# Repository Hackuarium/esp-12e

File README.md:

| GPIO  |            |           |         |                                           |            | Arduino |                  |
| ----- | ---------- | --------- | ------- | ----------------------------------------- | ---------- | ------- | ---------------- |
| 0     |            | SPI_CS2   |         | HIGH: normal, LOW: programming            | LOW / HIGH | D3      | button LOW / BLK |
| 1     |            | SPI_CS1   | U0_TXD  |                                           | TX         | D10     | TX               |
| 2     |            |           | U1_TXD  | on boot HIGH for programming              | HIGH       | D4      | One WIRE (HIGH)  |
| 3     |            |           | U0_RXD  |                                           | RX         | D9      | RX               |
| 4     |            |           |         |                                           | I2C        | D2/SDA  | SDA              |
| 5     |            |           |         |                                           | I2C        | D1/SCL  | SCL              |
| 6     | SDIO_CLK   | SPI_CLK   |         | used to connect flash 4MB                 | reserved   |
| 7     | SDIO_DATA0 | SPI_MISO  |         | used to connect flash 4MB                 | reserved   |
| 8     | SDIO_DATA1 | SPI_MOSI  | U1_RXD  | used to connect flash 4MB                 | reserved   |
| 9     | SDIO_DATA2 | SPI_HD    | HSPI_HD | used to connect flash 4MB                 | reserved   |
| 10    | SDIO_DATA3 | SPI_WP    | HSPI_WP | used to connect flash 4MB                 | reserved   |
| 11    | SDIO_CMD   | SPI_CS0   |         | used to connect flash 4MB                 | reserved   |
| 12    | MTDI       | HSPI_MISO |         |                                           | MISO       | D6      | PWM R            |
| 13    | MTCK       | HSPI_MOSI | U0_CTS  |                                           | MOSI       | D7      | PWM G            |
| 14    | MTMS       | HSPI_CLK  |         |                                           | CLK        | D5      | PWM B            |
| 15    | MTDO       | HSPI_CS   | U0_RTS  | on boot LOW for programming               | LOW / CS   | D8      | PWM W (LOW)      |
| 16    | XPD_DCDC   |           |         | sleep mode to EXT_RSTB (allow deep sleep) | RESET      | D0      | RST              |
| 17    | ADC        |           |         | voltage 0—1.0V                            | Battery    | A0      |
| RESET |            |           |         |                                           |            |         | Pull UP          |

15: WS2812, adressable led

Read information on: https://www.kloppenborg.net/images/blog/esp8266/esp8266-esp12e-specs.pdf

Available pins: http://www.rabbithacks.com/esp8266/esp12-e-directly-usable-gpio-pins/

PWM on all the pins !
HSPI (screen or other): 12 13 14 15
PWM: R12 G15 B13
ADC: TOUT
I2C: SCL14 SDA2

## Flashing board ?

You need to maintain `SW2` while pressing `SW1` (reset) in order to set the ESP-12E in programing mode.

- https://hackaday.com/2015/03/18/how-to-directly-program-an-inexpensive-esp8266-wifi-module/
- https://easyeda.com/olegos76/ESP8266_arduino_IDE-d4457f9439fd4de7a8970ff36a4957d6
- https://www.instructables.com/id/3-Simple-Ways-of-Programming-an-ESP8266-12X-Module/
- https://www.codeproject.com/Articles/1152777/Programming-a-standalone-ESP-using-Arduino-IDE-and

## Programming from the arduino a nodeMcu

- https://www.instructables.com/id/Quick-Start-to-Nodemcu-ESP8266-on-Arduino-IDE/
- https://www.instructables.com/id/ESP8266-controlling-Neopixel-LEDs-using-Arduino-ID/

## MQTT+Node-RED

https://randomnerdtutorials.com/esp8266-and-node-red-with-mqtt/

With SSL (secure)? :

https://medium.com/@flespi/how-to-connect-esp8266-to-secure-mqtt-broker-know-it-all-and-get-it-done-approach-c33b94f37d88

https://hackaday.io/project/163666-secure-esp8266-mqtt-poc/log/158992-secure-mqtt-broker-setup

## FreeRTOS

It seems impossible to program the ESP-12E with RTOS from the Arduino IDE.

The SDK is maintained by Expressif and it svailable on:

https://github.com/espressif/ESP8266_RTOS_SDK

You will also find on this page the instructions to install the SDK

## Functions

- RGBW
- PCA9685 + 4 x BSP75
- WS2812 : addressable led
- Luminosity: TCS3400 or VEML6040 or VEML7700
- Pressure: MS5637
- Humidity / Temperature: ChipCAP2 or Si7021
- Power monitoring

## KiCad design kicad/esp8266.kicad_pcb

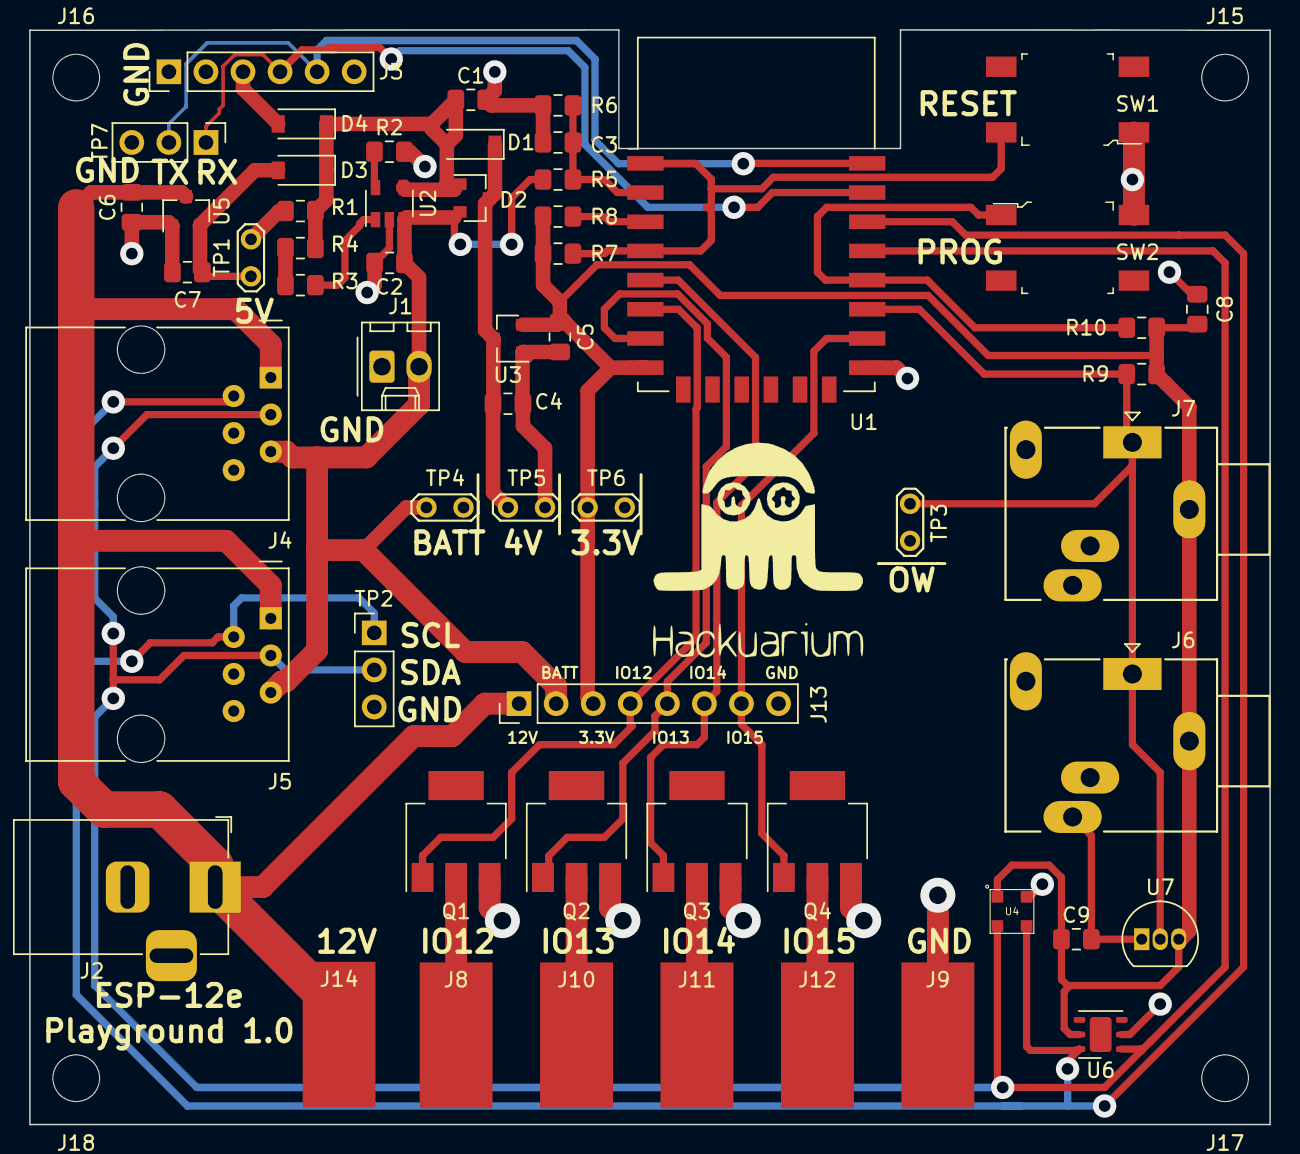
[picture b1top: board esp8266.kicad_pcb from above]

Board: 2 copper layers, 85.0 x 75.0 mm, 61 parts (0 on the bottom side), 28 nets.

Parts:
C1, C2, C8, C9: 10uF; C_0805_2012Metric_Pad1.15x1.40mm_HandSolder
C3: 100nF; C_0805_2012Metric_Pad1.15x1.40mm_HandSolder
C4, C5, C6, C7: 1uF; C_0805_2012Metric_Pad1.15x1.40mm_HandSolder
D1, D3, D4: D_Schottky; D_SOD-123
D2: DMP1045U; SOT-23
J1: BATT; Molex_KK-254_AE-6410-02A_1x02_P2.54mm_Vertical
J2: 5 / 12V; BarrelJack_Horizontal
J3: CONN FT232RL; PinHeader_1x06_P2.54mm_Vertical
J4, J5: RJ12-I2C; RJ12_Amphenol_54601
J6, J7: Onewire; Jack_3.5mm_Ledino_KB3SPRS_Horizontal
J8: Red; SolderWirePad_1x01_SMD_5x10mm
J9: Pad; SolderWirePad_1x01_SMD_5x10mm
J10: Green; SolderWirePad_1x01_SMD_5x10mm
J11: Blue; SolderWirePad_1x01_SMD_5x10mm
J12: White; SolderWirePad_1x01_SMD_5x10mm
J13: IO_RGBW; PinHeader_1x08_P2.54mm_Vertical
J14: +12V; SolderWirePad_1x01_SMD_5x10mm
J15, J16, J17, J18: hole; MountingHole_3.2mm_M3
Q1, Q2, Q3, Q4: BSP75; SOT-223
R1: 100k; R_0805_2012Metric_Pad1.15x1.40mm_HandSolder
R2, R3, R4, R7, R8, R10: 10k; R_0805_2012Metric_Pad1.15x1.40mm_HandSolder
R5: 1M; R_0805_2012Metric_Pad1.15x1.40mm_HandSolder
R6: 270k; R_0805_2012Metric_Pad1.15x1.40mm_HandSolder
R9: 4.7k; R_0805_2012Metric_Pad1.15x1.40mm_HandSolder
SW1: RESET; Switch_Tactile_SMD_6x6mm
SW2: PROG; Switch_Tactile_SMD_6x6mm
TP1: 5V; TestPoint_2Pads_Pitch2.54mm_Drill0.8mm
TP2: Test_i2C; PinHeader_1x03_P2.54mm_Vertical
TP3: OneWire; TestPoint_2Pads_Pitch2.54mm_Drill0.8mm
TP4: V_BAT; TestPoint_2Pads_Pitch2.54mm_Drill0.8mm
TP5: V_OUT; TestPoint_2Pads_Pitch2.54mm_Drill0.8mm
TP6: 3.3V; TestPoint_2Pads_Pitch2.54mm_Drill0.8mm
TP7: Test_UART; PinHeader_1x03_P2.54mm_Vertical
U1: ESP-12E
U2: MCP73831-2; SOT-23-5
U3: MCP1703-33; SOT-23
U4: MS5637
U5: MCP1703-50; SOT-23
U6: Si7020-A20; DFN-6-1EP_3x3mm_P1mm_EP1.5x2.4mm
U7: DS18B20; TO-92_Inline

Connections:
+3V3: C5.2, C8.1, C9.1, J6.S, J7.S, J13.3, R7.1, R8.1, R9.1, R10.1, TP6.1, U1.8, U3.2, U4.1, U6.5, U7.3
+12V: C6.2, J2.1, J4.1, J5.1, J13.1, J14.1, U5.3
+BATT: C2.1, D2.2, J1.2, J4.5, J5.5, J13.2, R5.1, TP4.1, U2.3
/ADC: C3.1, R5.2, R6.1, U1.2
/EN: R8.2, U1.3
/IO2: J6.T, J7.T, R9.2, TP3.1, U1.17, U7.2
/IO12: J13.4, Q1.1, U1.6
/IO13: J13.5, Q2.1, U1.7
/IO14: J13.6, Q3.1, U1.5
/IO15: J13.7, Q4.1, U1.16
/MCP1703-33/VDD: C4.2, D1.1, D2.3, TP5.1, U3.3
/MCP1703-50/5.0V: C7.2, D3.2, TP1.1, U5.2
/MCP73831/VIN: C1.1, D1.2, D2.1, D3.1, D4.1, R1.1, R4.2, U2.4
/MCP73831/V_STATUS: R3.2, R4.1
/RST: R7.2, SW1.2, U1.1, U1.4
/RX: J3.4, TP7.1, U1.21
/SCL: J4.2, J5.2, TP2.1, U1.20, U4.3, U6.6
/SDA: J4.3, J5.3, TP2.2, U1.19, U4.2, U6.1
/TX: J3.5, TP7.2, U1.22
/VCC_FTDI: D4.2, J3.3
GND: C1.2, C2.2, C3.2, C4.1, C5.1, C6.1, C7.1, C8.2, C9.2, J1.1, J2.2, J3.1, J4.4, J4.6, J5.4, J5.6, J6.R, J7.R, J9.1, J13.8, Q1.3, Q2.3, Q3.3, Q4.3, R1.2, R2.2, R6.2, SW1.1, SW2.2, TP1.2, TP2.3, TP3.2, TP4.2, TP5.2, TP6.2, TP7.3, U1.15, U2.2, U3.1, U4.4, U5.1, U6.2, U7.1
unnamed: J8.1, Q1.2
unnamed: J10.1, Q2.2
unnamed: J11.1, Q3.2
unnamed: J12.1, Q4.2
unnamed: R2.1, U2.5
unnamed: R3.1, U2.1
unnamed: R10.2, SW2.1, U1.18

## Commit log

2019-01-12 some info
2019-01-12 add beginning of pcb
2019-01-13 improve kicad
2019-01-15 add 18B20 on board
2019-01-16 correst bsp75 footprint
2019-01-17 add test points in kicad
2019-01-18 add more test points
2019-01-18 working on routing
2019-01-19 first pcb v1.0
2019-01-19 final version of V100
2019-01-20 add distances
2019-01-22 move 3d models to shared library
2019-01-22 move sub schemas
2019-01-22 pub back hackuarium logo on pcb
2019-02-03 improve label position
2019-04-09 fix readme
2019-04-09 fix resistor on IO15 and button
2019-05-02 Test to get battery level
2019-05-02 Test for blinking outputs 12-15 (Vin can be 5V or 12V according to the adapter plugged)
